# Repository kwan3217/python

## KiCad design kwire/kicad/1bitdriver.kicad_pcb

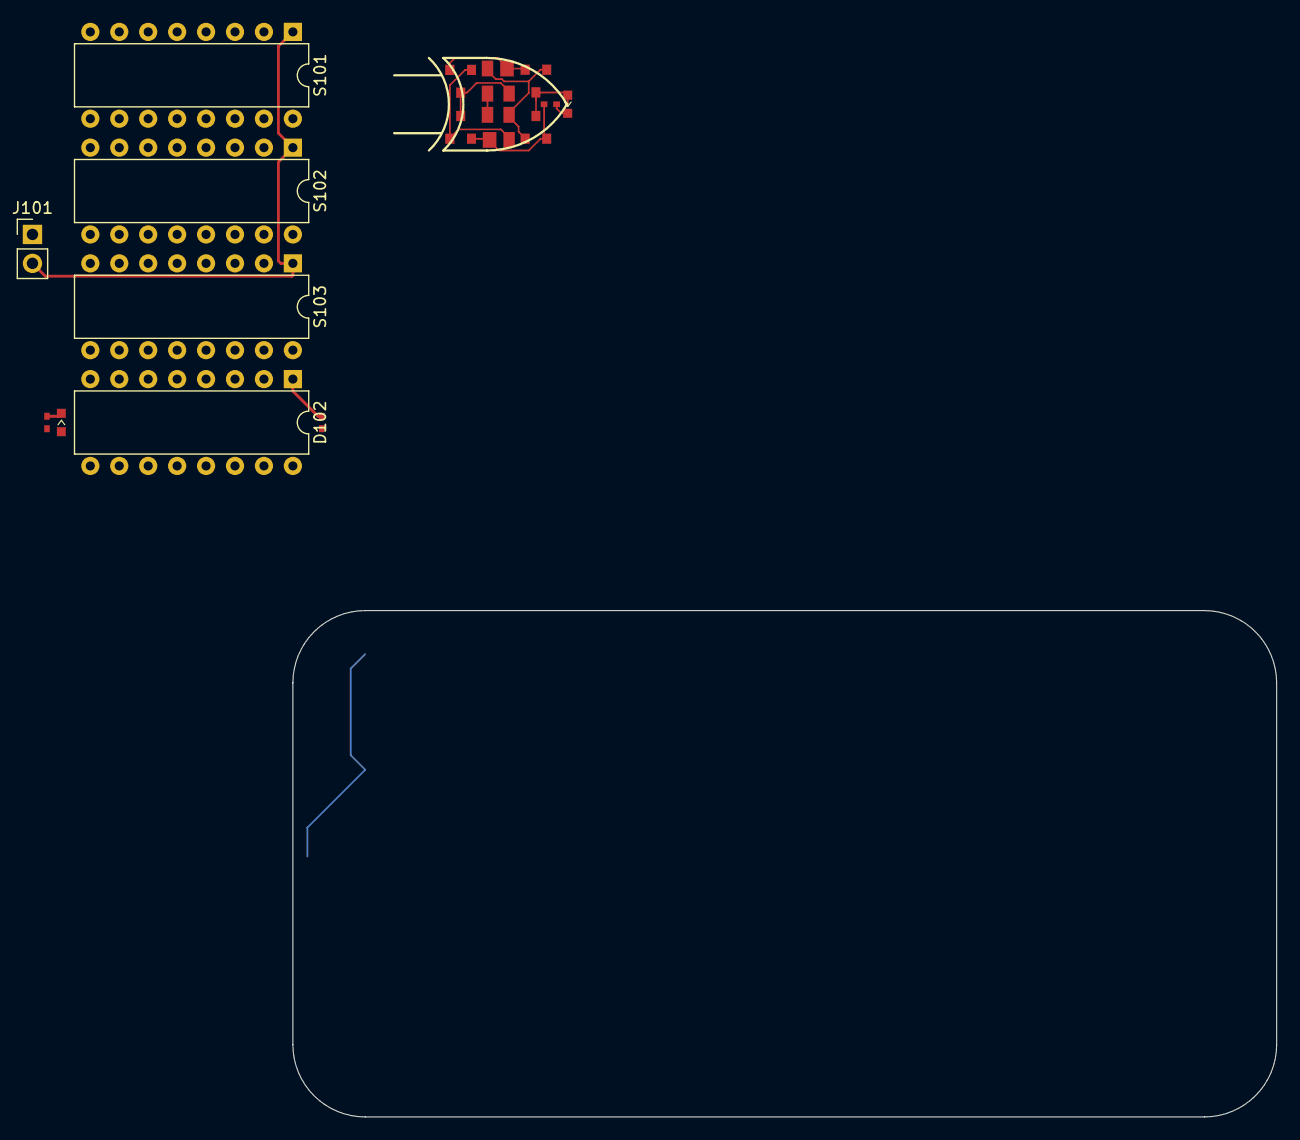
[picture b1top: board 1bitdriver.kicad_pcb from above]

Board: 2 copper layers, 86.4 x 44.4 mm, 16 parts (0 on the bottom side), 10 nets.

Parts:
D101: K; D_0603
D102: S; DIP-16_W7.62mm
D201: Y; D_0603
J101: CONN_01X02; Pin_Header_Straight_1x02_Pitch2.54mm
Q201, Q205: PMOS; SOT-23
Q202, Q206: NMOS; SOT-23
Q203: PMOS_BODY; SOT-143
Q204: NMOS_BODY; SOT-143
R101, R102, R201: RESISTOR; SMD_0402
S101: A; DIP-16_W7.62mm
S102: B; DIP-16_W7.62mm
S103: C; DIP-16_W7.62mm

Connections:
/A: Q201.1, Q202.1, Q204.2, S101.16
/B: Q203.3, Q204.4, S102.16
/bit0/#A: Q201.3, Q202.3, Q203.4
/bit0/#Y: Q203.2, Q204.3, Q205.1, Q206.1
/bit0/Y: D201.2, Q205.3, Q206.3
/bit0/Y-: D201.1, R201.1
GND: J101.1, Q202.2, Q204.1, Q206.2, R101.2, R102.2, R201.2, S101.8, S102.8, S103.8
unnamed: D101.1, R101.1
unnamed: D102.1, R102.1
VCC: J101.2, Q201.2, Q203.1, Q205.2, S101.1, S102.1, S103.1

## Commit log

2016-12-30 Renamed project file
2016-12-30 Added .gitignore
2016-12-30 Added Virtual Computer
2016-12-30 Added routines to calculate moment of inertia
2017-01-01 Added moments of inertia
2017-06-07 Moved dance from Processing to Python
2017-06-10 Shifting terms works, but hit an obstacle with terms in fractions. That's going to have to be a separate dance move
2017-07-13 Adding python kwire
2017-07-14 Added a .gitignore to mathdance
2017-07-14 Starting over from KicadSimple.g4
2017-07-14 Preliminary Kicad grammar finished. Removed grammars which were only for helping me learn antlr
2017-07-15 More work on Makefile
2017-07-17 Changed to using a Visitor instead of a Listener
2017-07-17 Tree reshaping now works
2017-07-18 Adding kwire stuff
2017-07-18 Starting to modify the Makefile so that grammars get compiled into their own folders
2017-07-19 Lots of work, 1bit adder now works
2017-07-19 Added 1-bit adder driver and control/indicator parts to library
2017-07-19 Use a heap to sort events
2017-07-19 Added addsub modules, which can do subtraction if you set the SUB input and carry_in inputs appropriately
2017-07-21 Tomo soldermask fix, adding kwire stuff
2017-07-21 More stuff
2017-07-22 Added xordriver, to test xor gate in kwire
2017-07-22 Filtered out kwire to support moving to the python repository
2017-07-22 Moved kicad files to a subfolder
2017-07-24 Adding start for parser for kicad_pcb files
2017-07-24 Forked the XOR.
    The 6-transistor XOR gate works fine, but depends on having access to the
    body terminal of the transistor. In an IC, all body terminals are connected to
    VCC (for PMOS) or GND (for NMOS), so that the gate voltages are relative to the
    power supply rails. Therefore, you can use NMOS as a high-side switch and PMOS
    as a low-side switch.
    The 6T gate depends on this, because the power rails for the middle inverter are
2017-07-24 Putting in gray code input enumerator
2017-07-31 Starting xtce packet parser
2017-08-01 Packet reader now working on pocketometer packets
2017-08-02 Now parses multiple files
2017-09-25 Added GlobeTrotter
2017-10-08 Added robot packet parser
2017-12-07 Converted Ranger7 kernel-maker from IDL to python
2017-12-12 More work with consistency checking of Ranger 7 table. This work helped to verify the spreadsheet.
2017-12-14 Added Kepler and Gauss problem to bmw
2017-12-15 More stuff on Ranger
2017-12-15 Use background metakernel
2017-12-15 Added Herrick-Gibbs method to BMW. Used it to try smoothing the velocity. Used Gauss to smooth complete trajectory, pos error <60m, vel error <1m/s
2017-12-21 Improving structure of code. Hopefully it will run soon :)
2017-12-22 Removed use of gradient descent
2017-12-22 More plotting and more surface impact reference points
2017-12-27 Starting on CK file
2017-12-29 Added CK kernel
2018-02-08 Renamed to vehicle, added more classes
2018-02-09 More work on pspacegear
2018-02-23 added monte carlo inertia estimator, to assist in testing the more exotic explicit inertia formulas
2018-02-23 Added spheroid inertia functions
2018-05-01 Added atmosphere and drag to PSpaceGear
2018-05-02 Added Atlas V 401, switched to Earth
2018-05-02 Starting to add propellant levels as integrator state
2018-05-03 Started vessel class, and refactoring of mass, drag, and thrust functions into it
2018-05-04 Started PEG
2018-05-04 Refactored resolving vectors into components. Started PEG
2018-05-04 Work on debugging PEG. It seems like one of the approximations isn't good enough, still looking at it.
2018-05-07 Used a more approximate approximation for DeltaV for when the original approximation (eqn36) fails
2018-05-07 Added script example to read a Google Sheet as a CSV
2018-05-07 Added some more stuff to pspacegear gitignore
2018-05-08 Adding porkchop calculator
2018-05-08 committing for merge
2018-05-08 Started to add calculation of arrival conditions
2018-05-09 Adding daf.py, for dumping Spice DAF (bsp and bc) files
2018-05-09 Added ETCAL printout
2018-05-09 Added CK processing
2018-05-15 Added back-propagation
2018-05-17 More work on optimizing launch trajectory
2018-05-18 More work on plotting PEG
2018-08-23 Adding MinecraftSurvey, a start to a program that can make a map from a 1.13 save
2018-08-26 Commiting for pull
2018-08-27 Adding code to actually read the chunk data and plot the inhabited time for each chunk
2018-09-08 Added charlieplex
2018-09-22 Added hard-coded packets for Southwest, added 64-bit integers, fixed-length strings, and endian control
2018-09-22 Added Pocketometer packets
2018-09-24 Initial checkin
2018-09-26 Added RMB parsing, fixed parsing of RMC and GGA
2018-09-26 Refactor to parse multiple files
2018-09-27 Refactoring, adding controllable skip
2018-12-28 Commenting out a bunch of unnecessary print statements
2018-12-28 spice/.idea/spice.iml
2019-01-11 Initial checkin of ahrs.py
2019-01-11 Adding ImportTest.py
2019-01-11 Adding visualization practice
2019-01-11 Added patch_serial, a poorly-named project which looks up picture timestamps, NMEA records, and compiles KML placemarks for the pictures
2019-01-22 Changing list of files to check
2019-01-22 Adding features
2019-01-24 Added render_sensinator, to render line plots of Sensinator data to overlay on videos
2019-01-25 Added code to animate Sensinator playback
2019-01-25 Adding blinnfit
2019-01-25 Added voyager supertrajectory camera heading calculator
2019-01-25 Added Ranger7Rectify, to semi-automatically identify reticle points on Ranger images
2019-01-25 Added code to calculate times of seasons
2019-01-25 Moved some exif/KML code to nmea
2019-01-25 Added code that wasn't checked in yet
2019-01-25 Moved some projects into subfolders
2019-01-25 Moved more projects to subfolders
2019-01-25 Added some more .gitignore
2019-01-25 Moved stuff out of pspacegear which isn't related to space simulation
2019-01-26 More read_sensinator stuff
2019-04-22 Adding code in anticipation of using the p5 processing-python library
2019-10-29 Adding Jupyter notebooks
2019-10-31 Commit prior to experiment with stripping of output in a git hook
2019-11-01 Added particle filter for comparison with unscented filter. Added RK4 integrator to improve accuracy.
2019-11-01 Added more text about how the 'size' of the Kalman gain describes the relative 'trust' we have in the estimate vs measurement
2019-11-17 Split out some stuff into subpages, more work on making things work with arrays and stacks of vectors
2019-12-07 Made Blinnfit actually do a fit to the stars
2019-12-19 Finished blinnfit and added fits for supertrajectory
2020-01-21 Addimg CMOD reader, translated from java
2020-01-22 Finished CMOD to OBJ converter, wrote a visualizer for CMOD objects
2020-03-11 A bunch of changes, including adding the start of Spice for the Kerbal system
2020-03-11 Preparing for pull
2020-06-29 Updating notebooks
2020-06-29 Adding requirements.txt
2020-10-01 Fixed bug with handling sclk number with whole-thousand instrument number
2021-02-17 Checkin for backup purposes
2021-05-29 Added data for STS-122 launch
2021-09-11 Copied from old MSL project
2021-09-11 Updated .gitignore to ignore outputs of edl.py
2021-09-11 Inverted the Z axis
2021-09-11 Show off the MSL Rover model by itself
2021-09-11 Added loc_look.inc
2021-09-11 Moved terrain model stuff to this project
2021-09-11 Added users of edl.py: MSL and M20, for pre-landing prediction and post-landing reconstruction
2021-09-11 Updated .gitignore. Added more stuff from old EDL project
2021-09-11 Added geogebra entry vehicle sketch
2021-09-11 Adding M2020 reconstruction pov files
